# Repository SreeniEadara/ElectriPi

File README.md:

# ElectriPi
A power supply shield for the Raspberry Pi. Capable of supplying up to 27.5W to the Raspberry Pi and 50W total including auxiliary output.

## Features
- Indicator LEDs for power in and power out
- 4040 cooling fan compatibility (fan voltage is selectable)
- Input reverse polarity protection
- Input protected by user-replacable fuse
- Input & output transient protection
- Switching frequency nominally out of audible range (no power supply whine under light loads)
- Raspberry Pi protected by ideal diode
- Auxillary 5V output

## Capabilities (predicted from component selection)
- Capable of powering all current RPi models with high current peripherals (27.5W max supplied to the Pi)
- High maximum auxiliary output power (22.5W or greater, depends on remainder of 50W total not consumed by RPi)
- Wide input range (7V - 24V)

TO BE TESTED:
- Max/min input range
- Max output current
- Protection performance
- Operating temperatures
- Output ripple and load response
- Efficiency

*Once these have been tested, I'll prepare an appropriate datasheet.*

NOTE: Device is, as of writing (Feb 2024), in the prototype phase. Details are SUBJECT TO CHANGE and specified performance characteristics are PRELIMINARY AND UNTESTED.

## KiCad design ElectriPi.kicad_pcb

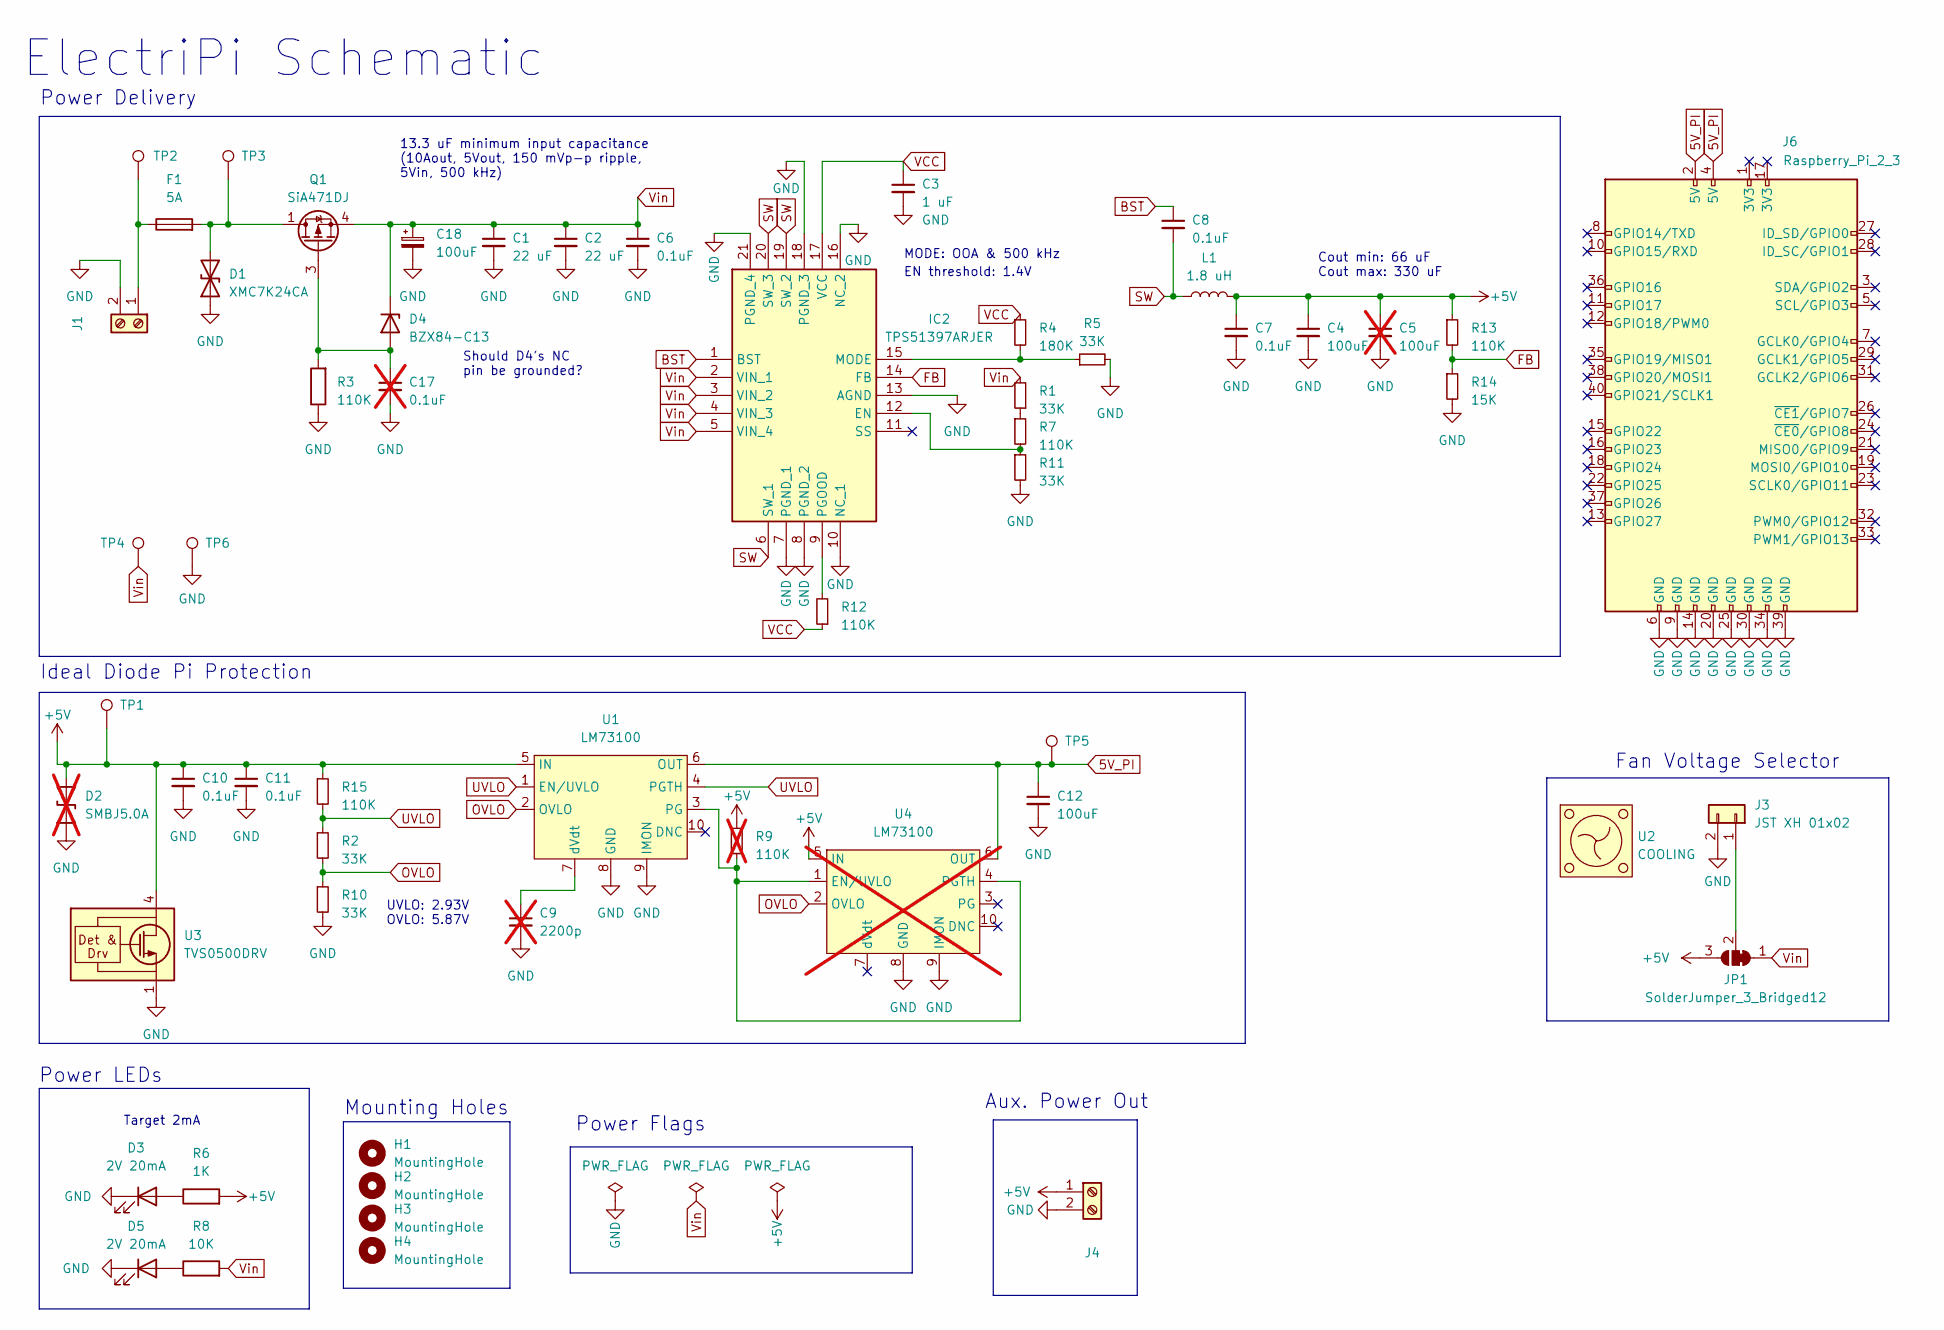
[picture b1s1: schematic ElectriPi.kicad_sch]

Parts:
C1, C2: 22 uF; C_0805_2012Metric; Mouser 810-C2012X5R1V226MAC
C3: 1 uF; C_0603_1608Metric; LCSC C15849
C4, C12: 100uF; C_1206_3216Metric; Mouser 81-GRM31CR61A107MA8L
C5: 100uF; C_1206_3216Metric; Mouser 81-GRM31CR61A107MA8L; not fitted
C6, C7, C8, C10, C11: 0.1uF; C_0402_1005Metric; Mouser 81-GRM155R62A104KE4J
C9: 2200p; C_0402_1005Metric; DigiKey 490-GCM155R71H222KA37JTR-ND; not fitted
C17: 0.1uF; C_0402_1005Metric; Mouser 81-GRM155R62A104KE4J; not fitted
C18: 100uF; CP_Elec_8x10; Mouser 80-EEV107M050S9MAA
D1: XMC7K24CA; D_SMC; Mouser 78-XMC7K24CAHM3/H
D2: SMBJ5.0A; D_SMB; DigiKey SMBJ5.0ALFTR-ND; not fitted
D3, D5: 2V 20mA; LED_0603_1608Metric; LCSC C72038
D4: BZX84-C13; SOT-23; Mouser 771-BZX84-C13-T/R
F1: 5A; Fuseholder_Blade_Mini_Keystone_3557; LCSC C352820
H1, H2, H3, H4: MountingHole; MountingHole_2.7mm_M2.5_DIN965_Pad
IC2: TPS51397ARJER; QFN-20-1EP_3x3mm_P0.45mm_EP1.6x1.6mm_ThermalVias; LCSC C1518754
J1, J4: 282837-2; TerminalBlock_bornier-2_P5.08mm; LCSC C592976
J3: JST XH 01x02; JST_XH_B2B-XH-A_1x02_P2.50mm_Vertical; LCSC C24193
J6: Raspberry_Pi_2_3; PinSocket_2x20_P2.54mm_Vertical; DigiKey 1568-PRT-16764-ND
JP1: SolderJumper_3_Bridged12; SolderJumper-3_P1.3mm_Bridged2Bar12_RoundedPad1.0x1.5mm
L1: 1.8 uH; L_Vishay_IHLP-4040; LCSC C506636
Q1: SiA471DJ; Vishay_PowerPAK_SC70-6L_Single; Mouser 78-SIA471DJ-T1-GE3
R1, R2, R5, R10, R11: 33K; R_0402_1005Metric; LCSC C323721
R3, R7, R12, R13, R15: 110K; R_0402_1005Metric; LCSC C413107
R4: 180K; R_0402_1005Metric; LCSC C413110
R6: 1K; R_0402_1005Metric; LCSC C409028
R8: 10K; R_0402_1005Metric; LCSC C270371
R9: 110K; R_0402_1005Metric; LCSC C413107; not fitted
R14: 15K; R_0402_1005Metric; LCSC C319837
TP1, TP2, TP3, TP4, TP5, TP6: TestPoint; TestPoint_Pad_D1.5mm
U1: LM73100; Texas_VQFN-HR-10_2x2mm_P0.475mm; DigiKey 296-LM73100RPWRTR-ND
U2: COOLING; 4040
U3: TVS0500DRV; WSON-6-1EP_2x2mm_P0.65mm_EP1x1.6mm; DigiKey 296-48382-2-ND
U4: LM73100; Texas_VQFN-HR-10_2x2mm_P0.475mm; DigiKey 296-LM73100RPWRTR-ND; not fitted

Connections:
5V_PI: C12.1, J6.2 (5V), J6.4 (5V), TP5.1, U1.6 (OUT), U4.6 (OUT)
+5V: C4.1, C5.1, C7.1, C10.1, C11.1, D2.2 (A2), J4.1, JP1.3 (B), L1.2, R6.2, R9.2, R13.1, R15.1, TP1.1, U1.5 (IN), U3.4 (IN), U3.5 (IN), U3.6 (IN), U4.5 (IN)
BST: C8.1, IC2.1 (BST)
FB: IC2.14 (FB), R13.2, R14.1
GND: C1.2, C2.2, C3.2, C4.2, C5.2, C6.2, C7.2, C9.2, C10.2, C11.2, C12.2, C17.2, C18.2, D1.1 (A1), D2.1 (A1), D3.1 (K), D5.1 (K), IC2.7 (PGND_1), IC2.8 (PGND_2), IC2.10 (NC_1), IC2.13 (AGND), IC2.16 (NC_2), IC2.18 (PGND_3), IC2.21 (PGND_4), J1.2, J3.2, J4.2, J6.6 (GND), J6.9 (GND), J6.14 (GND), J6.20 (GND), J6.25 (GND), J6.30 (GND), J6.34 (GND), J6.39 (GND), R3.1, R5.2, R10.2, R11.2, R14.2, TP6.1, U1.8 (GND), U1.9 (IMON), U3.1 (GND), U3.2 (GND), U3.3 (GND), U3.7 (GND), U4.8 (GND), U4.9 (IMON)
unnamed: D1.2 (A2), F1.2, Q1.1 (D), TP3.1
unnamed: D3.2 (A), R6.1
unnamed: C17.1, D4.1 (A), Q1.3 (G), R3.2
unnamed: D5.2 (A), R8.1
unnamed: IC2.12 (EN), R7.2, R11.1
unnamed: IC2.15 (MODE), R4.2, R5.1
unnamed: IC2.9 (PGOOD), R12.2
unnamed: F1.1, J1.1, TP2.1
unnamed: J3.1, JP1.2 (C)
unnamed: R1.1, R7.1
unnamed: R9.1, U1.3 (PG), U4.1 (EN/UVLO), U4.4 (PGTH)
unnamed: C9.1, U1.7 (dVdt)
OVLO: R2.2, R10.1, U1.2 (OVLO), U4.2 (OVLO)
SW: C8.2, IC2.6 (SW_1), IC2.19 (SW_2), IC2.20 (SW_3), L1.1
UVLO: R2.1, R15.2, U1.1 (EN/UVLO), U1.4 (PGTH)
VCC: C3.1, IC2.17 (VCC), R4.1, R12.1
Vin: C1.1, C2.1, C6.1, C18.1, D4.3 (K), IC2.2 (VIN_1), IC2.3 (VIN_2), IC2.4 (VIN_3), IC2.5 (VIN_4), JP1.1 (A), Q1.4 (S), R1.2, R8.2, TP4.1

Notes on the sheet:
Ideal Diode Pi Protection
Mounting Holes
Target 2mA
MODE: OOA & 500 kHz
Fan Voltage Selector
Cout min: 66 uF Cout max: 330 uF
ElectriPi Schematic
13.3 uF minimum input capacitance (10Aout, 5Vout, 150 mVp-p ripple, 5Vin, 500 kHz)
EN threshold: 1.4V
Should D4's NC pin be grounded?
Aux. Power Out
Power Flags
Power LEDs
UVLO: 2.93V OVLO: 5.87V
Power Delivery

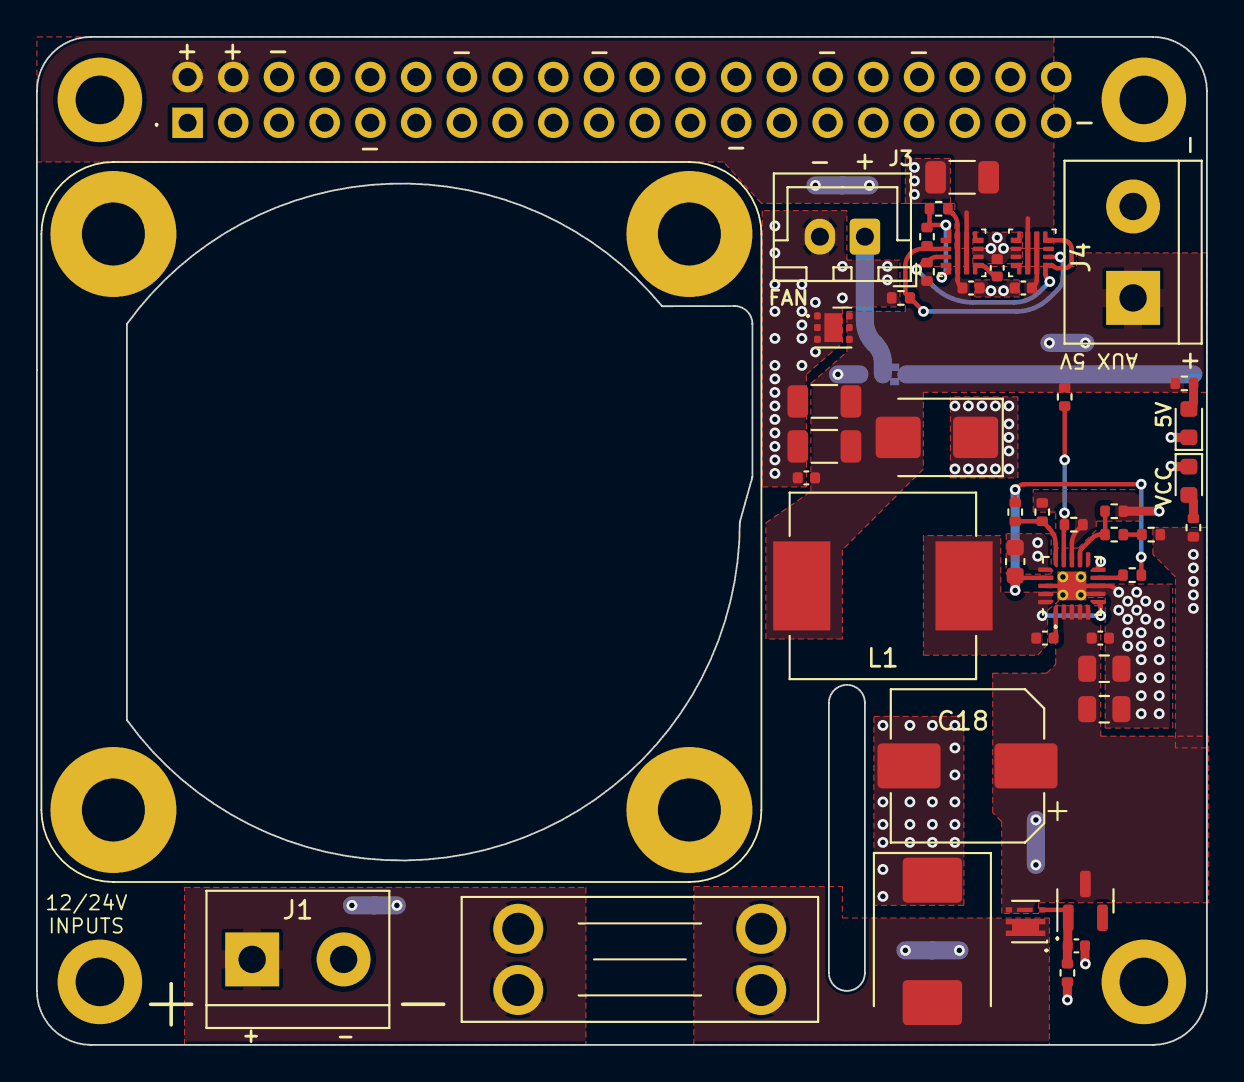
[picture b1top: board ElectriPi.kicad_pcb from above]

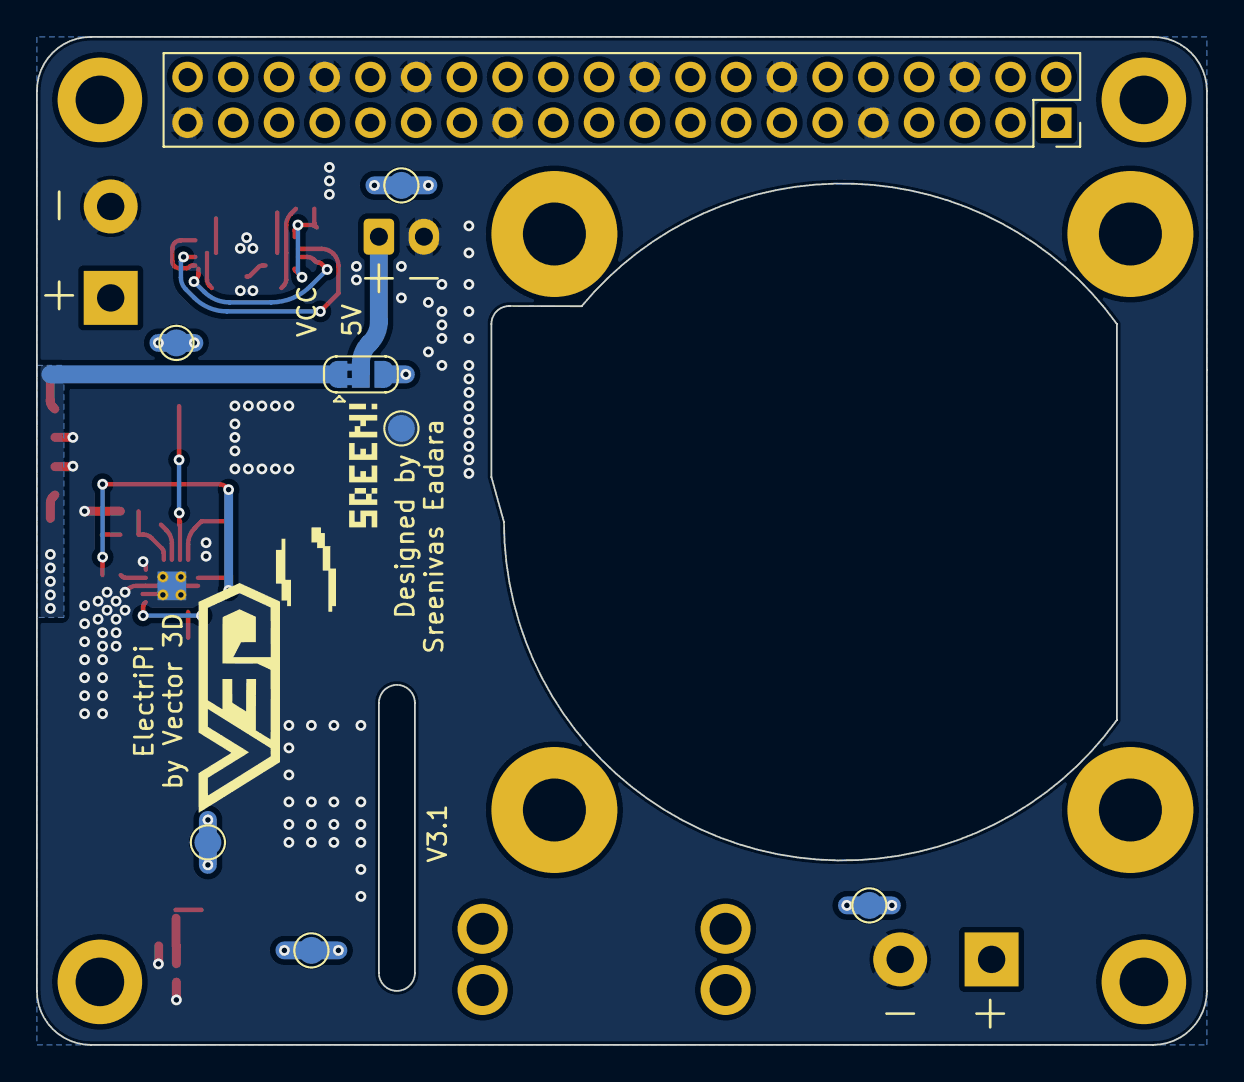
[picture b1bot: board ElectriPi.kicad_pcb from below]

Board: 2 copper layers, 65.0 x 56.0 mm, 57 parts (8 on the bottom side), 22 nets.

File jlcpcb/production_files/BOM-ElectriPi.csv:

Comment,Designator,Footprint,LCSC
5A,F1,Fuse_Littelfuse-NANO2-451_453,C108518
2444,J1,TerminalBlock_4Ucon_1x02_P3.50mm_Horizontal,C123214
TPS51397ARJER,IC2,QFN-20-1EP_3x3mm_P0.45mm_EP1.6x1.6mm_ThermalVias,C1518754
1 uF,C3,C_0603_1608Metric,C15849
100uF,C18,CP_Elec_8x10,C2165366
22 uF,"C1,C11,C12,C2",C_0805_2012Metric,C2179409
0.1uF,"C10,C13,C14,C15,C17,C6,C7,C8,C9",C_0402_1005Metric,C2193622
JST XH 01x02,"J2,J3,J8",JST_XH_B2B-XH-A_1x02_P2.50mm_Vertical,C24193
1K,R6,R_0402_1005Metric,C25087
10K,R8,R_0402_1005Metric,C25867
LM74700,U1,SOT-23-6,C2941042
100uF,"C4,C5",C_1206_3216Metric,C312983
15K,R14,R_0402_1005Metric,C319837
33K,"R1,R11,R5",R_0402_1005Metric,C323721
XMC7K24CA,D1,D_SMC,C3712593
110K,"R12,R13,R3,R7",R_0402_1005Metric,C413107
180K,R4,R_0402_1005Metric,C413110
PESD5V0C1BSFYL,D6,Nexperia_DSN0603-2_0.6x0.3mm_P0.4mm,C477955
1.8 uH,L1,L_Vishay_IHLP-4040,C506636
2.3V 20mA,"D3,D5",LED_0603_1608Metric,C72038
SiA430DJT,Q2,Vishay_PowerPAK_SC70-6L_Single,C727347
BZX84-C13,D4,SOT-23,C87090
SiA471DJ,Q1,Vishay_PowerPAK_SC70-6L_Single,

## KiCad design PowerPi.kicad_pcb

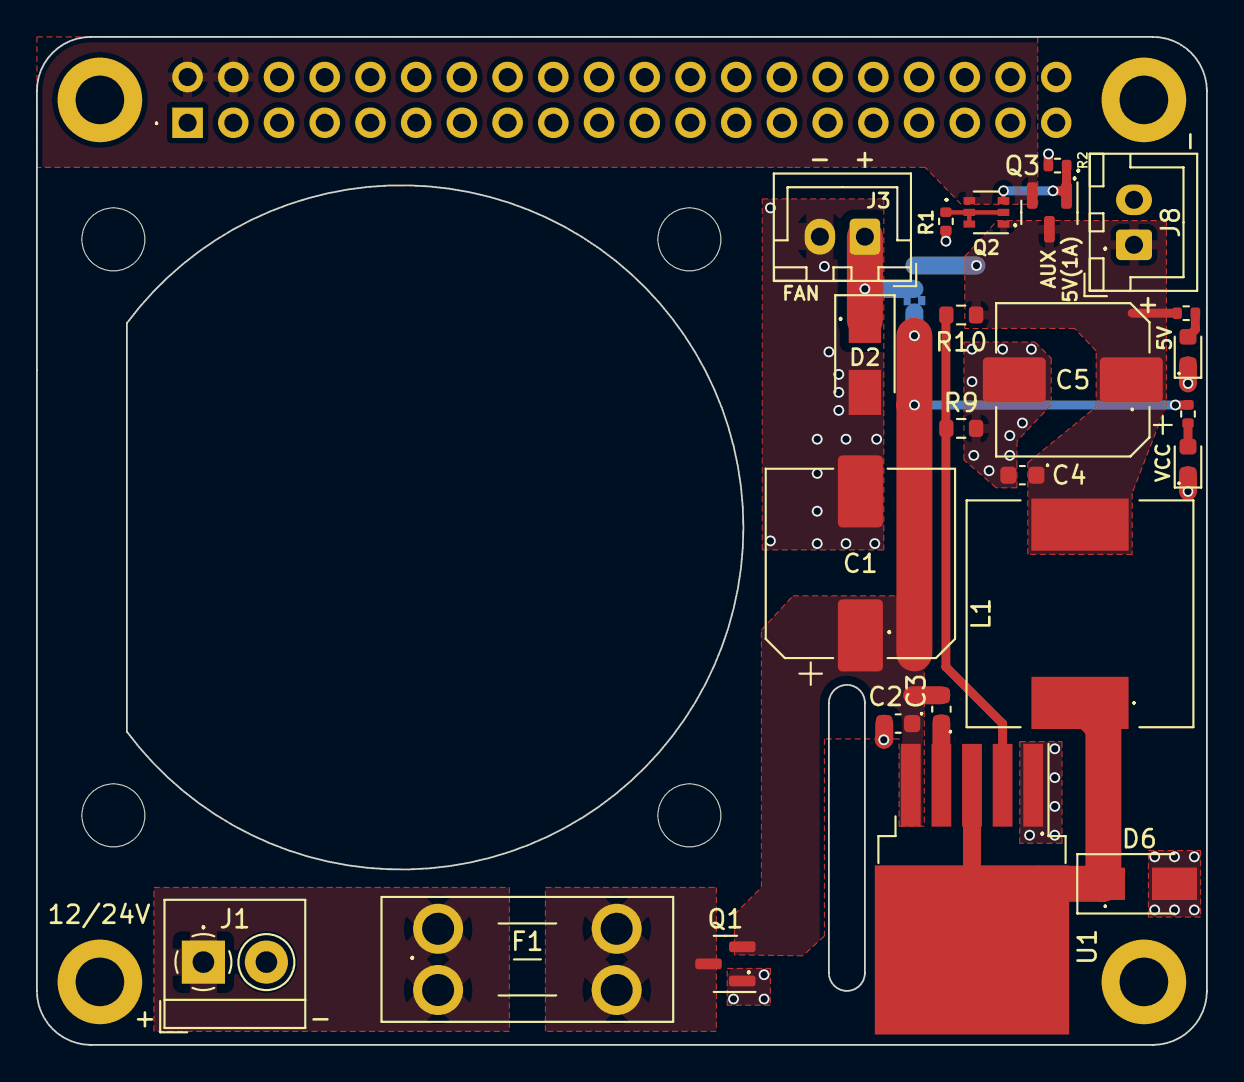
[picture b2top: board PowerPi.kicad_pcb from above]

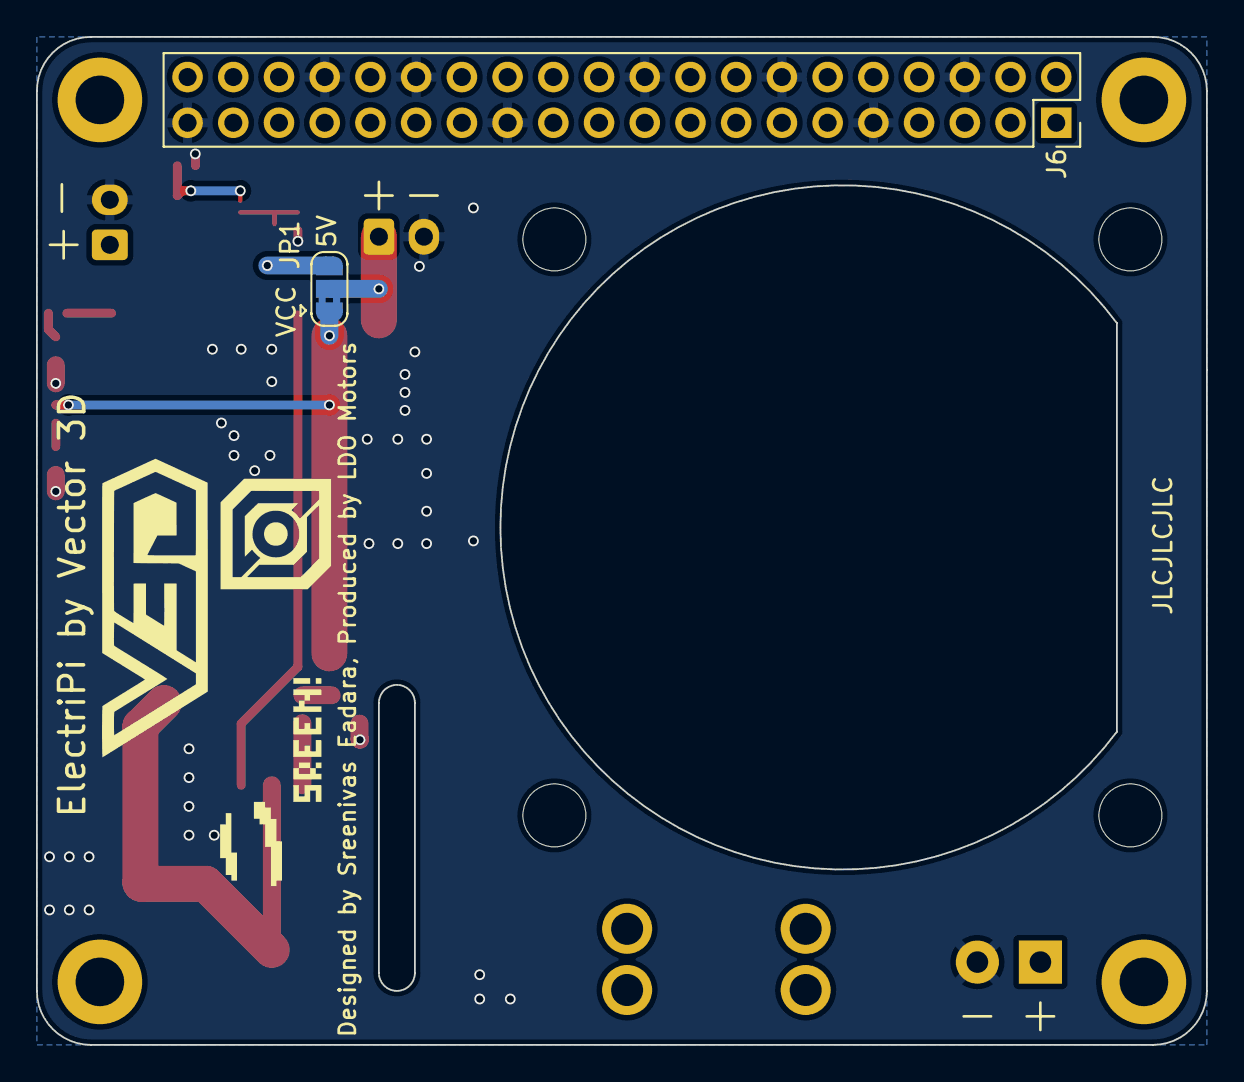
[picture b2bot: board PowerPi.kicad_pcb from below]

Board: 2 copper layers, 65.0 x 56.0 mm, 34 parts (2 on the bottom side), 14 nets.

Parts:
C1: 220uF; CP_Elec_10x10
C2, C3, C4: 1 uF; C_0603_1608Metric
C5: 1000uF; CP_Elec_8x10
D2, D6: SS54; D_SMA
D3, D5: 2.3V 20mA; LED_0603_1608Metric
F1: 5A; Fuseholder_Blade_Mini_Keystone_3568
H1, H2, H3, H4: MountingHole; MountingHole_2.7mm_M2.5_DIN965_Pad
H5, H6, H7, H8: MountingHole; MountingHole_3.5mm
J1: 2444; TerminalBlock_4Ucon_1x02_P3.50mm_Horizontal
J3, J8: JST XH 01x02; JST_XH_B2B-XH-A_1x02_P2.50mm_Vertical
J6: Raspberry_Pi_2_3; PinSocket_2x20_P2.54mm_Vertical
JP1: SolderJumper_3_Bridged12; SolderJumper-3_P1.3mm_Bridged2Bar12_RoundedPad1.0x1.5mm
L1: 47 uH; L_12x12mm_H6mm
Q1, Q3: 30V 4A 44mΩ; SOT-23
Q2: 50nA 150V 200mW 200mA; SOT-363_SC-70-6
R1: 10K; R_0402_1005Metric
R2: 47K; R_0402_1005Metric
R6: 1kR; R_0402_1005Metric
R8: 10kR; R_0402_1005Metric
R9: 3.3K; R_0603_1608Metric
R10: 10K; R_0603_1608Metric
U1: XL4015; TO-263-5_TabPin3

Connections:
5V_PI: J6.2 (5V), J6.4 (5V), Q2.4 (E2), Q3.2 (S)
+5V: C4.1, C5.1, J8.1, JP1.3 (B), L1.2, Q2.1 (E1), Q3.3 (D), R6.2, R10.2
GND: C1.2, C2.2, C4.2, C5.2, D2.2 (A), D3.1 (K), D5.1 (K), D6.2 (A), J1.2, J3.2, J6.6 (GND), J6.9 (GND), J6.14 (GND), J6.20 (GND), J6.25 (GND), J6.30 (GND), J6.34 (GND), J6.39 (GND), J8.2, Q1.1 (G), R1.2, R2.2, R9.2, U1.1 (GND)
unnamed: C3.1, U1.4 (VC)
unnamed: D2.1 (K), J3.1, JP1.2 (C)
unnamed: D3.2 (A), R6.1
unnamed: D5.2 (A), R8.1
unnamed: D6.1 (K), L1.1, U1.3 (SW)
unnamed: F1.1, J1.1
unnamed: F1.2, Q1.3 (D)
unnamed: Q2.2 (B1), Q2.5 (B2), Q2.6 (C1), R1.1
unnamed: Q2.3 (C2), Q3.1 (G), R2.1
unnamed: R9.1, R10.1, U1.2 (FB)
VCC: C1.1, C2.1, C3.2, JP1.1 (A), Q1.2 (S), R8.2, U1.5 (VIN)

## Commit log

2022-04-28 repairing files
2022-04-28 more file repair
2022-04-30 Updating to add freewheeling diodes, power LEDs, etc.
2022-05-01 adding footprints assignment to sch
2022-05-01 currently under development. Layout in progress
2022-05-02 changed out fuseholder, mounting holes, headers, removed i2c, etc
2022-05-02 cleanup and added proper JLC number for fuseholder
2022-05-03 Layout V1 complete
2022-05-03 Create LICENSE
2022-05-04 Adding panelization between breakouts. Updated layout and component position.
2022-05-05 remove breakout board and add +5V out
2022-05-06 Cleanup and miscellaneous changes. Changed fuseholder and FET
2022-05-06 Minor Updates and Cleaning
    Changed JLC field to LCSC
    Changed Aux power output to JST XH
    Small changes to silkscreen labels to hide below components once fitted
    Added connector name labels to Frontsilk
2022-05-06 added additional silkscreen
2022-05-06 BOM Updates
    Mounting holes and other items not sent to automated manufacture excluded from BOM
2022-05-06 BOM and Gerber Generated
    BOM and Gerber Generated. Files sent for manufacture V0.1
2022-05-11 PCBway export and minor changes
    V0.1.1 files generated for PCBway with B.Mask included.
    Dot added to Pin 1 on F.silk
    Added Metadata to work with PCBway BOM
2022-05-12 Part Numbers for Littelfuse removed.
2022-05-18 bug fixes
2022-05-22 changing project name to remove 'HAT' designation
2022-05-25 changed input capacitors to 0402 footprint and updated layout to reduce EMI
2022-05-26 improved copper balance
2022-07-06 update to 1000 uF output electrolytic capacitor
2022-07-11 Production Changes
    Added LDO Naming to R.silk
    Fan JST XH pin +5 and GND swapped to match standard fans
    5V pwr LED resistor was 200R now 1KR
    24v pwr LED was 1.5k now 10k
    Changed sch symbol for XH to not have screws
    Added boxes to schematic layout
2022-07-12 V1.0 Release
    Silkscreen adjustments
2022-07-12 changing project name
2022-07-12 add back LICENSE
2022-08-02 Bladefuse holder switched to Littelfuse nano 2 fuse holder
2022-12-05 F.Silk, Fan passthough, Fuse, XH input and designator changes
    - Added more pin notes to 40Pin GPIO
    - Added cutout to fan hole to allow passthrough from reverse mounting
    - customised F1 Littelfuse footprint to correctly suit NANO 2 footprint
    - Add JST XH Input Option
    - Moved superfluous reference designators to hidden layer (user2)
2022-12-07 Adding ICL footprint and schematic symbol
2022-12-07 adding test points
2022-12-14 Some small adjustment to silkscreen
    rotated TP on b.silk to match other text
    hid reference text for pin socket
    hid reference text for ICL
2022-12-14 small BOM updates
2022-12-15 Adding Mouser part number for ICL
2022-12-19 adding GND test point
2022-12-19 Back Silkscreen Adjustments
    Test point reference labels now hidden.
    Adjusted credentials to match ElectriPi Mini
2022-12-20 Changed thermal reliefs for ICL connection to pours
2022-12-20 Final Tweaks ready for production
2023-01-17 Remove outdated .csv
2023-01-17 removing osx indexing file
2023-05-12 Updating gitignore to avoid osx junk file
2023-05-13 Update diode to thermally improved V30K45, silk altered, footprints updated, slight movement
2023-05-13 Change fan mounting holes to pads and remove JLCJLCJLC
2023-05-14 Remove reference designators on fan mounting holes
2023-05-27 Major Overhaul. Changed buck regulator to TPS51397ARJER. Changed Ideal Diode protection to NFET and LM74700. Changed to higher ID FETs for reverse power protection and ideal diode. Omitted inrush pro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
2023-05-27 switch to TVS diode that protects TPS51397ARJER
2023-05-27 Specify Inductor
2023-05-28 Reduce power consumption of gate protection
2023-05-28 Add remaining footprint assignments
2023-05-28 Adding input and output caps on the ideal diode and bypass caps on connectors
2023-05-29 Change to 18V zener
2023-05-29 Change PFET to higher current capable PFET
2023-05-30 Change value of Zener
2023-06-04 Some BOM consolidation, changed input TVS diode, altered ideal diode output capacitance
2023-06-05 Some changes to improve readability
2023-06-05 Remove 4 way junction
2023-06-17 First pass of layout complete
2023-06-17 Added back JLC
2023-06-18 Some cleanup and updated logo to avoid ERC warnings
2023-06-20 Added question to sch
2023-06-26 Small cleanup
2023-07-18 changes to copper pours to satisfy DRC
2023-07-19 Changed to higher current inductor, which had larger footprint
2023-07-23 Add bulk capacitance and update cap size
2023-07-23 update holdup capacitance
2023-07-27 Changed back to 0805 35V input caps. With added bulk capacitance derating less of a concern. Cleanup
2023-07-29 added distributor part numbers for several components
2023-08-03 BOM updates
    Fixed edge.cuts with fan and updated BOM
2023-10-13 Relocate silk dot
2024-01-28 Add DigiKey PN's
2024-01-28 increase hole size for easier manufacture
2024-01-28 alter thermal reliefs
2024-01-30 Change input connector to 5.08mm pitch. DNP caps on connectors. Remove JLC silk
2024-01-30 Remove outdated manf and BOM files
2024-01-30 update BOM
2024-01-30 Updated fuseholder to Keystone 3557 - low profile mini ATO fuses.
2024-01-31 regenerate BOM
2024-02-01 Update via sizes and board setup to meet manf constraints also changed dims of thermals on TPS51397A footprint
2024-02-01 change design rules and update manf outputs
2024-02-01 update gitignore
2024-02-03 updated BOM, gerbers, and symbol fields (mouser and LCSC PNs updated, useless fields removed)
2024-02-03 Fix pours, set board origin, regenerate gerbers
2024-02-06 update to new output surge/TVS protection suitable for DC supply. Still require manf output and bom regeneration.
2024-02-07 Improve PCB layout and regenerate manf files
2024-02-07 hide fan from BOM
2024-02-07 remove tmp file
2024-02-08 Add BOM exclusions for THT and DNP
2024-02-09 Update component position and add silk dots for pin 1
2024-02-09 Remove user.drawings rect
2024-02-09 Fix libraries and updated back silk
2024-02-10 Remove JST input / output connectors! Not rated for currents
2024-02-10 Adding a README
2024-02-11 Change ideal diode controller! Prev. would allow 0.6A rev current. New will block at 50 mA
2024-02-11 Updated layout to new ideal diode controller part and passives. Need to regen manf outputs.
2024-02-11 Rounded tracks
2024-02-11 Update manf outputs
2024-02-12 Change to LM73100. Much better suited for application
2024-02-12 Layout, need manf output regen
2024-02-12 Round tracks
2024-02-12 Update manf outputs and add VQFN-HR 10 Pin model from Gary Shores
2024-02-14 Move pours to avoid inductor core. Create SiA471DJ symbol
2024-02-18 regenerate manf outputs
2024-02-18 Update LM73100 with vendor part numbers
2024-02-18 Updating LED Mouser and Digikey PNs to MSL2 part. All parts now MSL2 or better
2024-02-20 Excluded DNP cap from BOM
2024-02-25 Preemptive changes following prototype order. DNP excess parts (output capacitance and extra ideal diode) and update README. Specify sourcing for 40 way header.
